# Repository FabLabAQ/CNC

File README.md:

# CNC

Migliorie da apportare alla CNC

[Lista della spesa](https://docs.google.com/spreadsheets/d/1Wq6bE2mLNkH-loEp1lNx39WeWIYjqB_c8ai0cWjN81c/edit?usp=sharing)

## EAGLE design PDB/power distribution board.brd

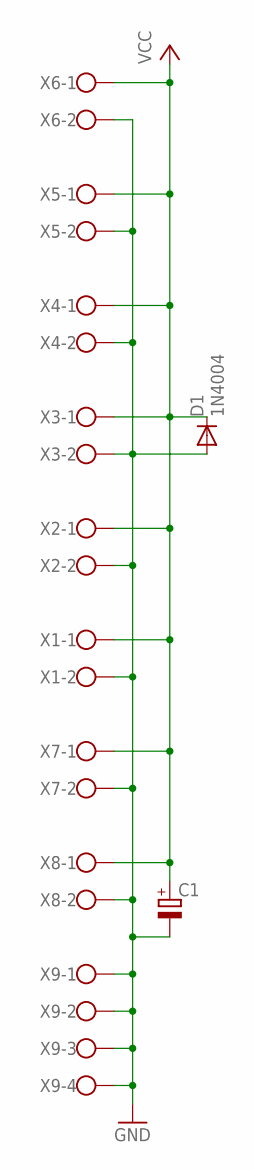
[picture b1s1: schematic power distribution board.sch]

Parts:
C1: CPOL-EUE5-10.5; E5-10,5
D1: 1N4004; DO41-10
X1, X2, X3, X4, X5, X6, X7, X8: W237-102
X9: W237-4

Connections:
GND: C1.-, D1.A, X1.2, X2.2, X3.2, X4.2, X5.2, X6.2, X7.2, X8.2, X9.1, X9.2, X9.3, X9.4
VCC: C1.+, D1.C, X1.1, X2.1, X3.1, X4.1, X5.1, X6.1, X7.1, X8.1

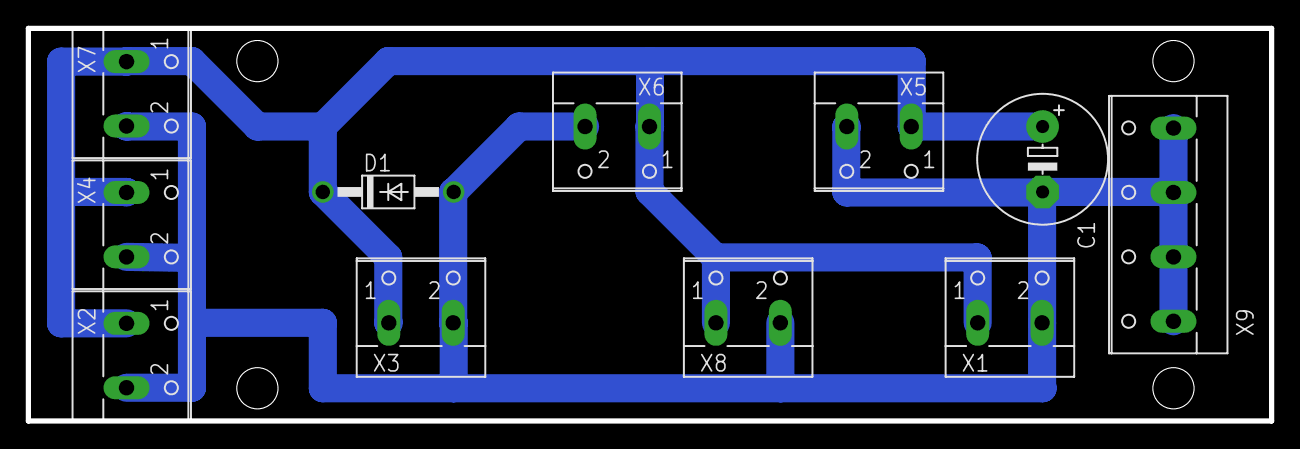
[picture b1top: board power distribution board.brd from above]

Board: 2 copper layers, 96.5 x 30.5 mm, 11 parts (0 on the bottom side), 2 nets.

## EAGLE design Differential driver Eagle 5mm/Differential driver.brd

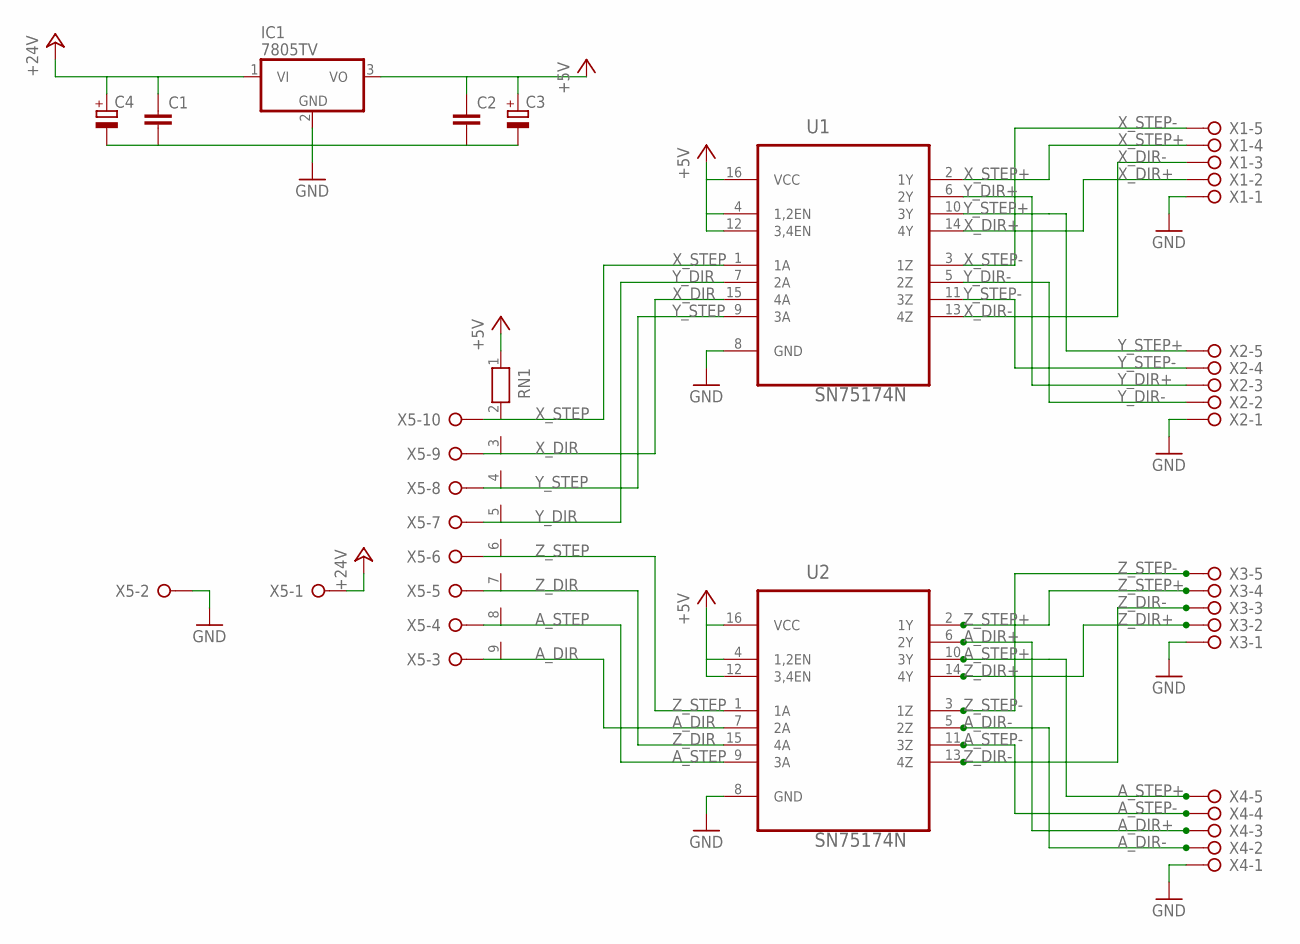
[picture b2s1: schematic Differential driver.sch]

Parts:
C1, C2: C-EU025-025X050; C025-025X050
C3, C4: CPOL-EUE2.5-5; E2,5-5
IC1: 7805TV; TO220V
RN1: RN08; RN-9
U1, U2: SN75174N; DIP254P762X508-16
X1, X2, X3, X4: W237-05P; W237-5P
X5: W237-10P

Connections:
+5V: C2.1, C3.+, IC1.3 (VO), RN1.1, U1.4 (1,2EN), U1.12 (3,4EN), U1.16 (VCC), U2.4 (1,2EN), U2.12 (3,4EN), U2.16 (VCC)
+24V: C1.1, C4.+, IC1.1 (VI), X5.1
A_DIR: RN1.9, U2.7 (2A), X5.3
A_DIR+: U2.6 (2Y), X4.3
A_DIR-: U2.5 (2Z), X4.2
A_STEP: RN1.8, U2.9 (3A), X5.4
A_STEP+: U2.10 (3Y), X4.5
A_STEP-: U2.11 (3Z), X4.4
GND: C1.2, C2.2, C3.-, C4.-, IC1.2 (GND), U1.8 (GND), U2.8 (GND), X1.1, X2.1, X3.1, X4.1, X5.2
X_DIR: RN1.3, U1.15 (4A), X5.9
X_DIR+: U1.14 (4Y), X1.2
X_DIR-: U1.13 (4Z), X1.3
X_STEP: RN1.2, U1.1 (1A), X5.10
X_STEP+: U1.2 (1Y), X1.4
X_STEP-: U1.3 (1Z), X1.5
Y_DIR: RN1.5, U1.7 (2A), X5.7
Y_DIR+: U1.6 (2Y), X2.3
Y_DIR-: U1.5 (2Z), X2.2
Y_STEP: RN1.4, U1.9 (3A), X5.8
Y_STEP+: U1.10 (3Y), X2.5
Y_STEP-: U1.11 (3Z), X2.4
Z_DIR: RN1.7, U2.15 (4A), X5.5
Z_DIR+: U2.14 (4Y), X3.2
Z_DIR-: U2.13 (4Z), X3.3
Z_STEP: RN1.6, U2.1 (1A), X5.6
Z_STEP+: U2.2 (1Y), X3.4
Z_STEP-: U2.3 (1Z), X3.5

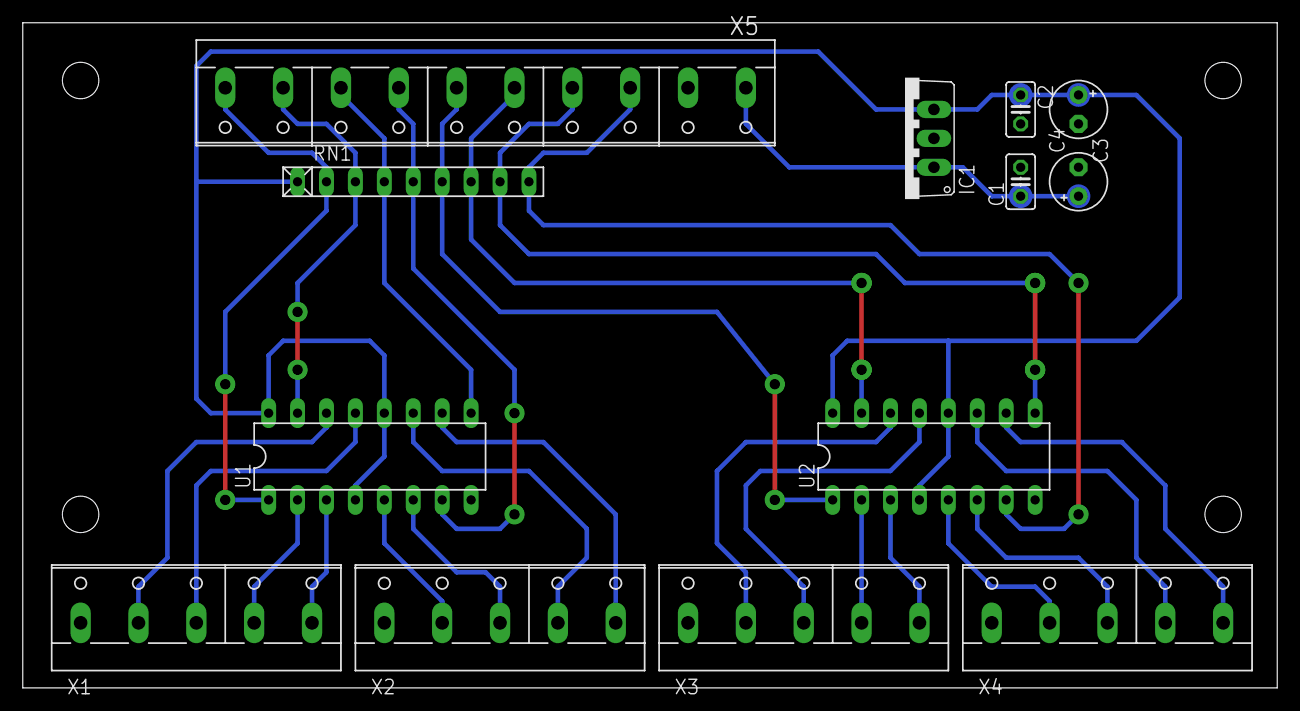
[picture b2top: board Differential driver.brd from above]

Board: 2 copper layers, 110.2 x 58.4 mm, 13 parts (0 on the bottom side), 27 nets.

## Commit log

2017-01-28 new docs
2017-02-05 differetial driver
2017-02-06 started electronics box
2017-02-07 driver update
2017-02-11 new driver version
2017-03-23 add A-axis servo
2017-07-05 conn panel
2017-07-25 handWheel
2017-07-26 back panel
